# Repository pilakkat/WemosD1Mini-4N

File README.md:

# Wemos D1 Mini 4 Node Smart Control

## 📌 Table of Contents

- [About the Project](#-about-the-project)
- [Screenshots](#-screenshots)
- [Usage](#-usage)
- [Configuration for Tasmota](#%EF%B8%8F-configuration-for-tasmota))

---

## 📖 About the Project

This board is designed as a multi-purpose board which can help in using the standard Wemos D1 Mini board based on ESP8266 to a 4 relay smart control unit. 
The relays are miniature in size which can control upto 5A, 250AC (or 7A, based on which unit you used). It has 4 inputs which can be connected to AC switch and 4 outputs can be connected to loads. The board can be fitted behind the switchboard as an after market fit without rewiring, provided there is a neutral line available. 

Additional taping points are added for using the device in many other configurations. Due to limited inputs, there is also 3 digital switch support based on ADC divider circuit provisioned. 

## 🖼 Screenshots

## 🚀 Usage
The design was done for using with Tasmota firmware, but user can use any firmware which can support the below configuraton.
- Inputs: D0, D1, D2, D3 and ADC (with voltage divider option for 3 digital pins)
- Outputs: D5, D5, D7 and D8

  Note: D3 has a pull-up and boot fails if pulled down during power on. 

D0 to D3 supports AC detection circuit. For using ADC divider based configuration, connect three switches between the marked joints (S1,S2,S3). All combinations of key presses and short circuits (SCB/SCG) are detectable via different ADC values if the default specified resistors are used. Other combinations could be used if only one or two switches are needed. 

Note: Refer BOM available under Gerber directory to see the component details.

## ⚙️ Configuration for Tasmota
Following configuration can be used for Tasmota firmware.

For AC detection circuit, you can also use following additional commands in tasmota console:
- switchdebounce0 109 : To set AC detection with 100ms debounce time
- switchmode0 1 : If you want to follow the manual switch instead of toggle every time

## 📜 License

This project is licensed under the MIT License

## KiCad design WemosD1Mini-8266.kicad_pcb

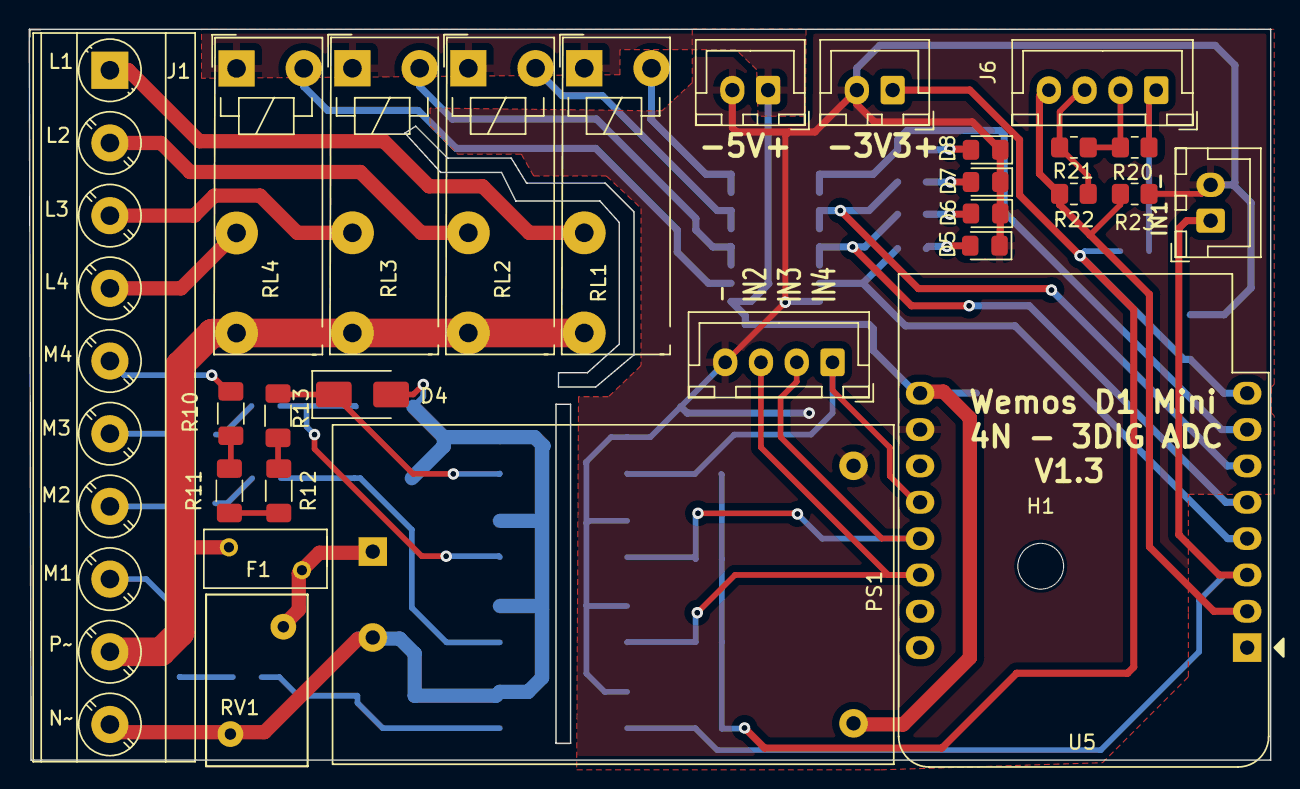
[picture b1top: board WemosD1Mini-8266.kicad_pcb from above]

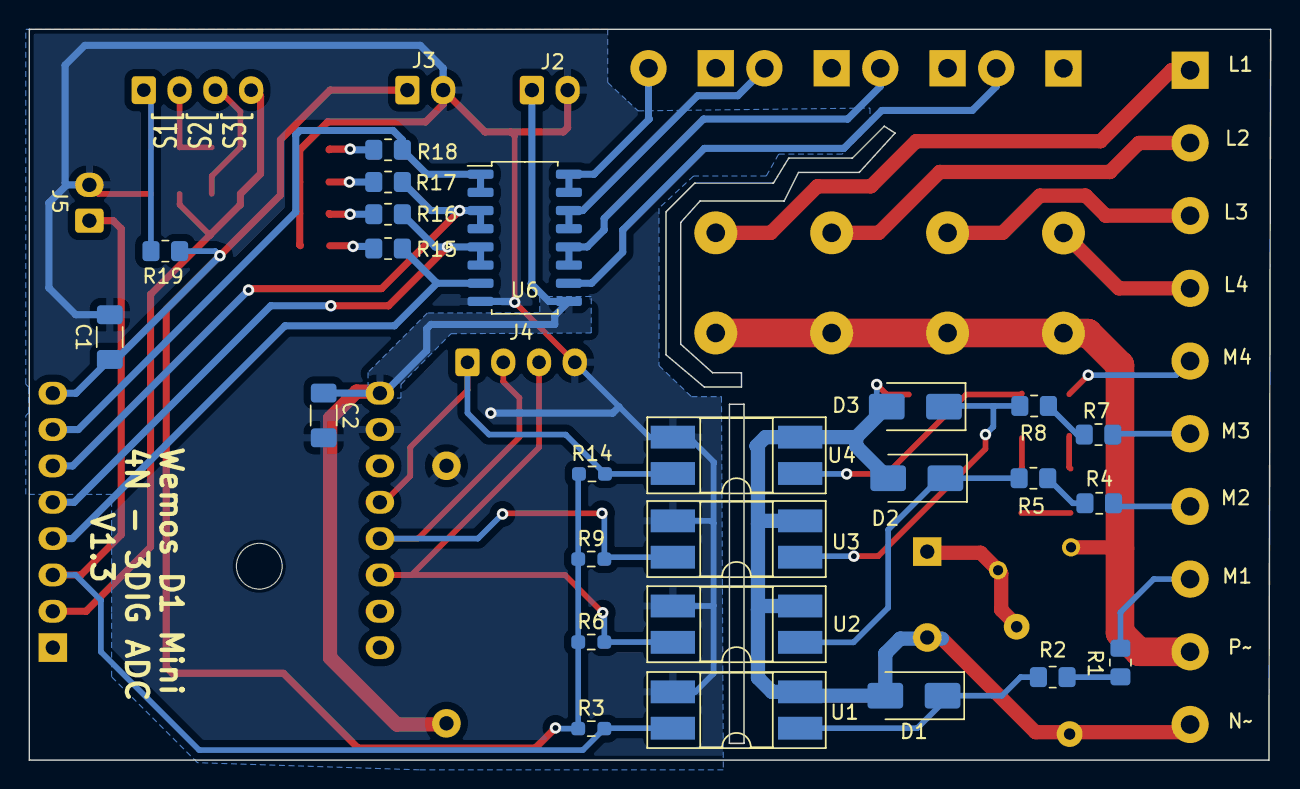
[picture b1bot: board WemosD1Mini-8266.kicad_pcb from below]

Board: 2 copper layers, 86.8 x 51.1 mm, 53 parts (25 on the bottom side), 44 nets.

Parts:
C1, C2: 0.1uF; C_1206_3216Metric_Pad1.33x1.80mm_HandSolder
D1, D2, D3, D4: 1N4007; D_SMA
D5, D6, D7, D8: LED; LED_0805_2012Metric_Pad1.15x1.40mm_HandSolder
F1: Fuse; Fuse_BelFuse_0ZRE0005FF_L8.3mm_W3.8mm
H1: MountingHole; MountingHole_3.2mm_M3
J1: Screw_Terminal_01x10; TerminalBlock_Phoenix_MKDS-3-10-5.08_1x10_P5.08mm_Horizontal
J2, J3, J5: Conn_01x02_Pin; JST_XH_B2B-XH-A_1x02_P2.50mm_Vertical
J4, J6: Conn_01x04_Pin; JST_XH_B4B-XH-A_1x04_P2.50mm_Vertical
PS1: HLK-5M05; Converter_ACDC_HiLink_HLK-5Mxx
R1, R2, R4, R5, R7, R8: 180K; R_0805_2012Metric_Pad1.20x1.40mm_HandSolder
R3, R6, R9, R14: 10K; R_0603_1608Metric_Pad0.98x0.95mm_HandSolder
R10, R11, R12, R13: 22K; R_1206_3216Metric_Pad1.30x1.75mm_HandSolder
R15, R16, R17, R18: 150; R_0805_2012Metric_Pad1.20x1.40mm_HandSolder
R19, R20: 470; R_0805_2012Metric_Pad1.20x1.40mm_HandSolder
R21: 1K; R_0805_2012Metric_Pad1.20x1.40mm_HandSolder
R22: 2.2K; R_0805_2012Metric_Pad1.20x1.40mm_HandSolder
R23: 1.5K; R_0805_2012Metric_Pad1.20x1.40mm_HandSolder
RL1, RL2, RL3, RL4: Relay_SPST-NO; Relay_THT_Hongfa HF46F SPST
RV1: Varistor; RV_Disc_D12mm_W7.1mm_P7.5mm
U1, U2, U3, U4: PC817; DIP-4_W8.89mm_SMDSocket_LongPads
U5: WeMos_D1_mini; WEMOS_D1_mini_light
U6: ULN2003; SOP-16_4.4x10.4mm_P1.27mm

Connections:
+3.3V: C1.1, J3.1, R3.1, R6.1, R9.1, R14.1, R19.2, U5.8 (3V3)
+5V: C2.1, J2.1, PS1.4 (+Vout), RL1.A1, RL2.A1, RL3.A1, RL4.A1, U5.9 (5V), U6.9 (COM)
/AC/L: F1.1, J1.9, RL1.14, RL2.14, RL3.14, RL4.14
/AC/L(P): F1.2, PS1.1 (AC/L), RV1.1
/AC/N: D1.2 (A), D2.2 (A), D3.2 (A), D4.2 (A), J1.10, PS1.2 (AC/N), RV1.2, U1.2, U2.2, U3.2, U4.2
/Load1: J1.4, RL4.13
/Load2: J1.3, RL3.13
/Load3: J1.2, RL2.13
/Load4: J1.1, RL1.13
/M1: J1.8, R1.1
/M2: J1.7, R4.1
/M3: J1.6, R7.1
/M4: J1.5, R10.1
/Relays/RL1: R15.1, U5.4 (SCK/D5), U6.7 (I7)
/Relays/RL2: R16.1, U5.5 (MISO/D6), U6.5 (I5), U6.6 (I6)
/Relays/RL3: R17.1, U5.6 (MOSI/D7), U6.3 (I3), U6.4 (I4)
/Relays/RL4: R18.1, U5.7 (CS/D8), U6.1 (I1), U6.2 (I2)
/Voltage Sensing/In1: J5.1, R3.2, U1.4, U5.3 (D0)
/Voltage Sensing/In2: J4.3, R6.2, U2.4, U5.14 (SCL/D1)
/Voltage Sensing/In3: J4.2, R9.2, U3.4, U5.13 (SDA/D2)
/Voltage Sensing/In4: J4.1, R14.2, U4.4, U5.12 (D3)
Earth: C1.2, C2.2, D5.1 (K), D6.1 (K), D7.1 (K), D8.1 (K), J2.2, J3.2, J4.4, J5.2, PS1.3 (-Vout), R23.2, U1.3, U2.3, U3.3, U4.3, U5.10 (GND), U6.8 (GND)
unnamed: D1.1 (K), R2.2, U1.1
unnamed: D2.1 (K), R5.2, U2.1
unnamed: D3.1 (K), R8.2, U3.1
unnamed: D4.1 (K), R13.2, U4.1
unnamed: D5.2 (A), R15.2
unnamed: D6.2 (A), R16.2
unnamed: D7.2 (A), R17.2
unnamed: D8.2 (A), R18.2
unnamed: J6.1, R19.1, R20.2
unnamed: J6.2, R20.1, R21.2
unnamed: J6.3, R21.1, R22.2
unnamed: J6.4, R22.1, R23.1, U5.2 (A0)
unnamed: R1.2, R2.1
unnamed: R4.2, R5.1
unnamed: R7.2, R8.1
unnamed: R10.2, R11.1
unnamed: R11.2, R12.1
unnamed: R12.2, R13.1
unnamed: RL1.A2, U6.15 (O2), U6.16 (O1)
unnamed: RL2.A2, U6.13 (O4), U6.14 (O3)
unnamed: RL3.A2, U6.11 (O6), U6.12 (O5)
unnamed: RL4.A2, U6.10 (O7)

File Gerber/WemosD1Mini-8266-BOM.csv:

"Id";"Designator";"Footprint";"Quantity";"Designation";"Supplier and ref";
1;"F1";"Fuse_BelFuse_0ZRE0005FF_L8.3mm_W3.8mm";1;"Fuse";;;
2;"U5";"WEMOS_D1_mini_light";1;"WeMos_D1_mini";;;
3;"RL3,RL1,RL2,RL4";"Relay_THT_Hongfa HF46F SPST";4;"Relay_SPST-NO";;;
4;"PS1";"Converter_ACDC_HiLink_HLK-5Mxx";1;"HLK-5M05";;;
5;"J5,J3,J2";"JST_XH_B2B-XH-A_1x02_P2.50mm_Vertical";3;"Conn_01x02_Pin";;;
6;"D4,D3,D1,D2";"D_SMA";4;"1N4007";;;
7;"D7,D5,D6,D8";"LED_0805_2012Metric_Pad1.15x1.40mm_HandSolder";4;"LED";;;
8;"J8";"TerminalBlock_Phoenix_MKDS-3-8-5.08_1x08_P5.08mm_Horizontal";1;"Screw_Terminal_01x08";;;
9;"R12,R13,R11,R10";"R_1206_3216Metric_Pad1.30x1.75mm_HandSolder";4;"22K";;;
10;"RV1";"RV_Disc_D12mm_W7.1mm_P7.5mm";1;"Varistor";;;
11;"R21";"R_0805_2012Metric_Pad1.20x1.40mm_HandSolder";1;"1K";;;
12;"H1";"MountingHole_3.2mm_M3";1;"MountingHole";;;
13;"J6,J4";"JST_XH_B4B-XH-A_1x04_P2.50mm_Vertical";2;"Conn_01x04_Pin";;;
14;"R23";"R_0805_2012Metric_Pad1.20x1.40mm_HandSolder";1;"1.5K";;;
15;"R20,R19";"R_0805_2012Metric_Pad1.20x1.40mm_HandSolder";2;"470";;;
16;"J1";"TerminalBlock_Phoenix_MKDS-3-10-5.08_1x10_P5.08mm_Horizontal";1;"Screw_Terminal_01x10";;;
17;"R22";"R_0805_2012Metric_Pad1.20x1.40mm_HandSolder";1;"2.2K";;;
18;"R4,R8,R5,R7,R2,R1";"R_0805_2012Metric_Pad1.20x1.40mm_HandSolder";6;"180K";;;
19;"R3,R9,R14,R6";"R_0603_1608Metric_Pad0.98x0.95mm_HandSolder";4;"10K";;;
20;"U6";"SOP-16_4.4x10.4mm_P1.27mm";1;"ULN2003";;;
21;"R15,R17,R18,R16";"R_0805_2012Metric_Pad1.20x1.40mm_HandSolder";4;"150";;;
22;"U4,U3,U2,U1";"DIP-4_W8.89mm_SMDSocket_LongPads";4;"PC817";;;
23;"C1,C2";"C_1206_3216Metric_Pad1.33x1.80mm_HandSolder";2;"0.1uF";;;

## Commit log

2025-02-03 Version 1
2025-02-03 Version 1 Gerber Files
2025-02-03 Added pics
2025-02-03 Update README.md
    Fix pic links
2025-02-03 Update README.md
    .
2025-02-03 Version 1.1
2025-02-03 Update pics
2025-02-03 Version 1.2 Updates.
    Added support for 3 digital switches via ADC. Added MOV+Fuse protection
2025-02-03 Gerber updates V1.2
2025-02-03 ReadMe updates
2025-02-03 Missing pics
2025-02-03 missing pcb bottom view pic
2025-02-07 V1.3 - Removed bypass PCB due to single design mandate from manufacturing.
2025-02-07 Pics update
